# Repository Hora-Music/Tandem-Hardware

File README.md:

Here are the eagle files of the Tandem Module 
The firmware and the manual are available at https://github.com/Hora-Music/Tandem

This hardware design is released under CC BY-NC-SA 4.0 License.

It contains both the main board, the schematics and the panel.
Even the panel is a PCB so everything can be made by a classic PCB manufacturer. 
It is up to you to decide the layer you want to use for the yellow silkscreen, 
some manufacturers don't accept two silkscreen colors. In that case you can set it to a copper/pad layer. 

The design contains pretty common components and is build around a simple (and unexpensive :) ) stmf103CBT6

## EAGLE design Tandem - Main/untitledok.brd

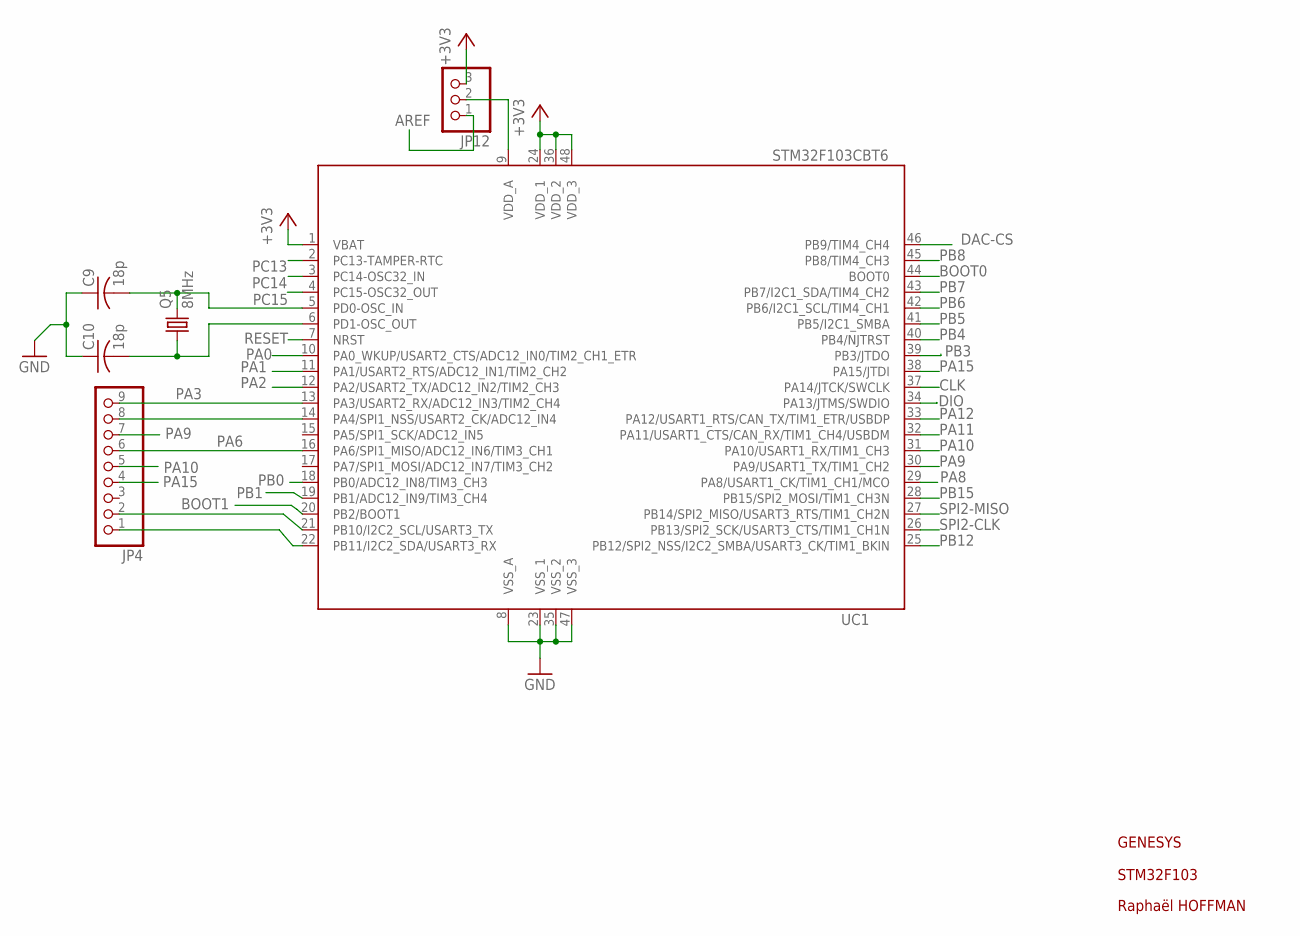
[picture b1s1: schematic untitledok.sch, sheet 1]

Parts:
C9, C10: 18p; C0603
JP4: PINHD-1X9; 1X09
JP12: PINHD-1X3; 1X03
Q5: 8MHz; HC49UP
UC1: STM32F103CBT6; LQFP48

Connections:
+3V3: JP12.3, UC1.1 (VBAT), UC1.24 (VDD_1), UC1.36 (VDD_2), UC1.48 (VDD_3); also elsewhere on the board
AREF: JP12.1; also elsewhere on the board
BOOT0: UC1.44 (BOOT0); also elsewhere on the board
BOOT1: UC1.20 (PB2/BOOT1); also elsewhere on the board
CLK: UC1.37 (PA14/JTCK/SWCLK); also elsewhere on the board
DAC-CS: UC1.46 (PB9/TIM4_CH4); also elsewhere on the board
DIO: UC1.34 (PA13/JTMS/SWDIO); also elsewhere on the board
GND: C9.1, C10.1, UC1.8 (VSS_A), UC1.23 (VSS_1), UC1.35 (VSS_2), UC1.47 (VSS_3); also elsewhere on the board
unnamed: JP12.2, UC1.9 (VDD_A)
unnamed: C9.2, Q5.2, UC1.5 (PD0-OSC_IN)
unnamed: C10.2, Q5.1, UC1.6 (PD1-OSC_OUT)
unnamed: JP4.1, UC1.22 (PB11/I2C2_SDA/USART3_RX)
unnamed: JP4.8, UC1.14 (PA4/SPI1_NSS/USART2_CK/ADC12_IN4)
unnamed: JP4.2, UC1.21 (PB10/I2C2_SCL/USART3_TX)
PA0: UC1.10 (PA0_WKUP/USART2_CTS/ADC12_IN0/TIM2_CH1_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); also elsewhere on the board
PA1: UC1.11 (PA1/USART2_RTS/ADC12_IN1/TIM2_CH2); also elsewhere on the board
PA2: UC1.12 (PA2/USART2_TX/ADC12_IN2/TIM2_CH3); also elsewhere on the board
PA3: JP4.9, UC1.13 (PA3/USART2_RX/ADC12_IN3/TIM2_CH4); also elsewhere on the board
PA6: JP4.6, UC1.16 (PA6/SPI1_MISO/ADC12_IN6/TIM3_CH1); also elsewhere on the board
PA8: UC1.29 (PA8/USART1_CK/TIM1_CH1/MCO); also elsewhere on the board
PA9: JP4.7, UC1.30 (PA9/USART1_TX/TIM1_CH2); also elsewhere on the board
PA10: JP4.5, UC1.31 (PA10/USART1_RX/TIM1_CH3); also elsewhere on the board
PA11: UC1.32 (PA11/USART1_CTS/CAN_RX/TIM1_CH4/USBDM); also elsewhere on the board
PA12: UC1.33 (PA12/USART1_RTS/CAN_TX/TIM1_ETR/USBDP); also elsewhere on the board
PA15: JP4.4, UC1.38 (PA15/JTDI)
PB0: UC1.18 (PB0/ADC12_IN8/TIM3_CH3); also elsewhere on the board
PB1: UC1.19 (PB1/ADC12_IN9/TIM3_CH4); also elsewhere on the board
PB3: UC1.39 (PB3/JTDO)
PB4: UC1.40 (PB4/NJTRST); also elsewhere on the board
PB5: UC1.41 (PB5/I2C1_SMBA); also elsewhere on the board
PB6: UC1.42 (PB6/I2C1_SCL/TIM4_CH1); also elsewhere on the board
PB7: UC1.43 (PB7/I2C1_SDA/TIM4_CH2); also elsewhere on the board
PB8: UC1.45 (PB8/TIM4_CH3); also elsewhere on the board
PB12: UC1.25 (PB12/SPI2_NSS/I2C2_SMBA/USART3_CK/TIM1_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); also elsewhere on the board
PB15: UC1.28 (PB15/SPI2_MOSI/TIM1_CH3N); also elsewhere on the board
PC13: UC1.2 (PC13-TAMPER-RTC); also elsewhere on the board
PC14: UC1.3 (PC14-OSC32_IN); also elsewhere on the board
PC15: UC1.4 (PC15-OSC32_OUT); also elsewhere on the board
RESET: UC1.7 (NRST); also elsewhere on the board
SPI2-CLK: UC1.26 (PB13/SPI2_SCK/USART3_CTS/TIM1_CH1N); also elsewhere on the board
SPI2-MISO: UC1.27 (PB14/SPI2_MISO/USART3_RTS/TIM1_CH2N); also elsewhere on the board

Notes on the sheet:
STM32F103
GENESYS
Raphaël HOFFMAN

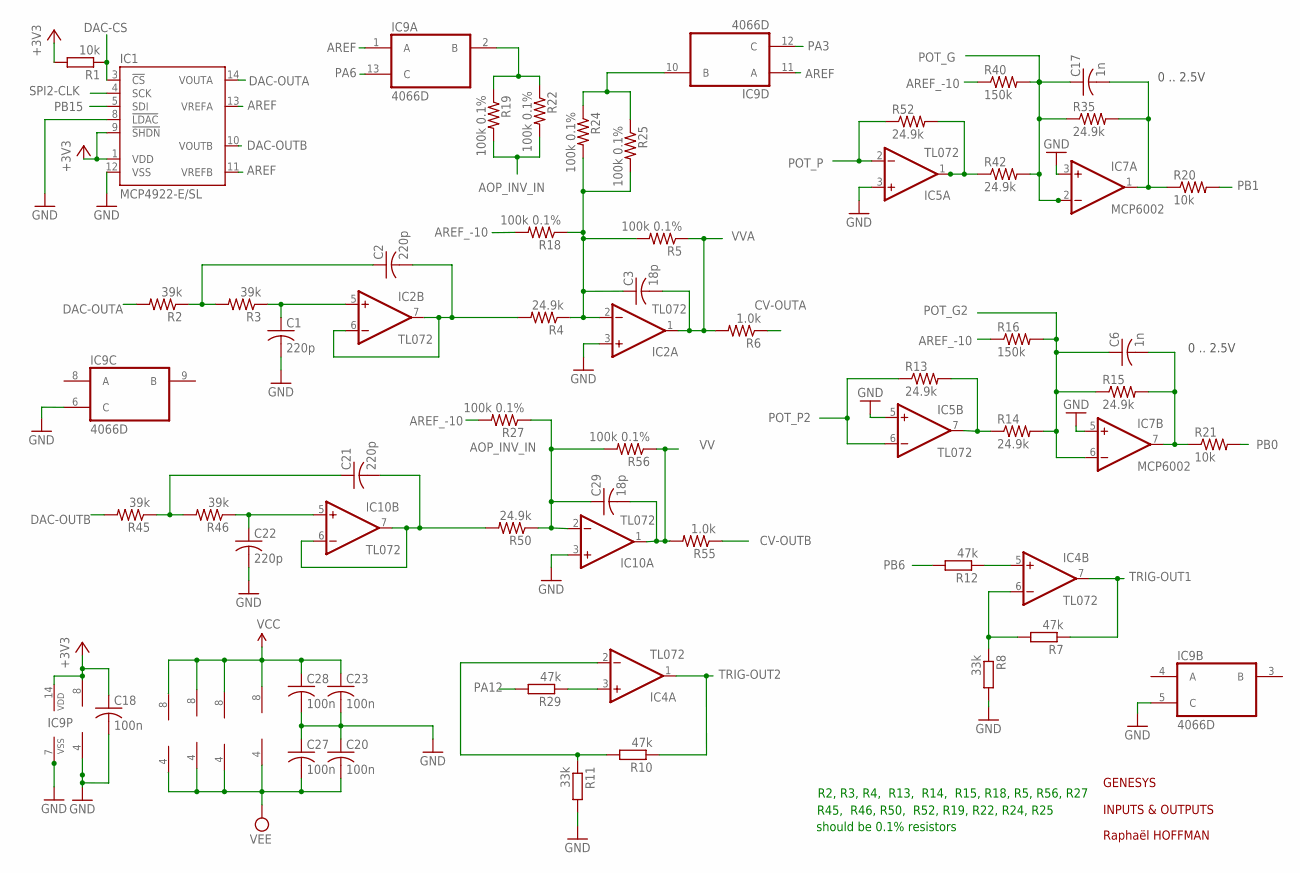
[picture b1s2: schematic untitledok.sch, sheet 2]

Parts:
C1, C2, C21, C22: 220p; C0603
C3, C29: 18p; C0603
C6, C17: 1n; C0603
C18, C20, C23, C27, C28: 100n; C0603
IC1: MCP4922-E/SL; SO14
IC2, IC4, IC5, IC10: TL072; SO08
IC7: MCP6002; SO08
IC9: 4066D; SO14
R1, R20, R21: 10k; R0603
R2, R3, R45, R46: 39k; R0603
R4, R13, R14, R15, R35, R42, R50, R52: 24.9k; R0603
R5, R18, R19, R22, R24, R25, R27, R56: 100k 0.1%; R0805
R6, R55: 1.0k; R0603
R7, R10, R12, R29: 47k; R0603
R8, R11: 33k; R0603
R16, R40: 150k; R0603

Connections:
+3V3: C18.1, IC1.1 (VDD), IC1.9 (!SHDN), IC7.8 (V+), IC9.14 (VDD), R1.2; also elsewhere on the board
AOP_INV_IN: C29.1, IC10.2 (-IN), R19.2, R22.2, R27.1, R50.1, R56.2
AREF: IC1.11 (VREFB), IC1.13 (VREFA), IC9.1 (A), IC9.11 (A); also elsewhere on the board
AREF_-10: R16.1, R18.2, R27.2, R40.1; also elsewhere on the board
CV-OUTA: R6.1; also elsewhere on the board
CV-OUTB: R55.1; also elsewhere on the board
DAC-CS: IC1.3 (!CS), R1.1; also elsewhere on the board
DAC-OUTA: IC1.14 (VOUTA), R2.2
DAC-OUTB: IC1.10 (VOUTB), R45.2
GND: C1.2, C18.2, C20.1, C22.2, C23.2, C27.1, C28.2, IC1.8 (!LDAC), IC1.12 (VSS), IC2.3 (+IN), IC5.3 (+IN), IC5.5 (+IN), IC7.3 (+IN), IC7.4 (V-), IC7.5 (+IN), IC9.5 (C), IC9.6 (C), IC9.7 (VSS), IC10.3 (+IN), R8.2, R11.2; also elsewhere on the board
unnamed: C2.2, IC2.6 (-IN), IC2.7 (OUT), R4.2
unnamed: C1.1, IC2.5 (+IN), R3.1
unnamed: C2.1, R2.1, R3.2
unnamed: IC4.3 (+IN), R29.1
unnamed: C3.1, IC2.2 (-IN), R4.1, R5.2, R18.1, R24.2, R25.2
unnamed: IC4.6 (-IN), R7.2, R8.1
unnamed: IC4.5 (+IN), R12.1
unnamed: IC5.7 (OUT), R13.2, R14.1
unnamed: IC9.2 (B), R19.1, R22.1
unnamed: IC4.2 (-IN), R10.2, R11.1
unnamed: IC9.10 (B), R24.1, R25.1
unnamed: IC5.1 (OUT), R42.1, R52.2
unnamed: C21.2, IC10.6 (-IN), IC10.7 (OUT), R50.2
unnamed: C22.1, IC10.5 (+IN), R46.1
unnamed: C21.1, R45.1, R46.2
P: C17.2, IC7.1 (OUT), R20.1, R35.2
PA3: IC9.12 (C); also elsewhere on the board
PA6: IC9.13 (C); also elsewhere on the board
PA12: R29.2; also elsewhere on the board
PB0: R21.2; also elsewhere on the board
PB1: R20.2; also elsewhere on the board
PB6: R12.2; also elsewhere on the board
PB15: IC1.5 (SDI); also elsewhere on the board
POT_G: C17.1, IC7.2 (-IN), R35.1, R40.2, R42.2; also elsewhere on the board
POT_G2: C6.1, IC7.6 (-IN), R14.2, R15.1, R16.2; also elsewhere on the board
POT_P: IC5.2 (-IN), R52.1; also elsewhere on the board
POT_P2: IC5.6 (-IN), R13.1; also elsewhere on the board
PPP: C6.2, IC7.7 (OUT), R15.2, R21.1
SPI2-CLK: IC1.4 (SCK); also elsewhere on the board
TRIG-OUT1: IC4.7 (OUT), R7.1; also elsewhere on the board
TRIG-OUT2: IC4.1 (OUT), R10.1; also elsewhere on the board
VCC: C23.1, C28.1, IC2.8 (V+), IC4.8 (V+), IC5.8 (V+), IC10.8 (V+); also elsewhere on the board
VEE: C20.2, C27.2, IC2.4 (V-), IC4.4 (V-), IC5.4 (V-), IC10.4 (V-); also elsewhere on the board
VV: C29.2, IC10.1 (OUT), R55.2, R56.1; also elsewhere on the board
VVA: C3.2, IC2.1 (OUT), R5.1, R6.2; also elsewhere on the board

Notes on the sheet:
0 .. 2.5V
INPUTS & OUTPUTS
GENESYS
Raphaël HOFFMAN
R2, R3, R4, R13, R14, R15, R18, R5, R56, R27
R45, R46, R50, R52, R19, R22, R24, R25
should be 0.1% resistors

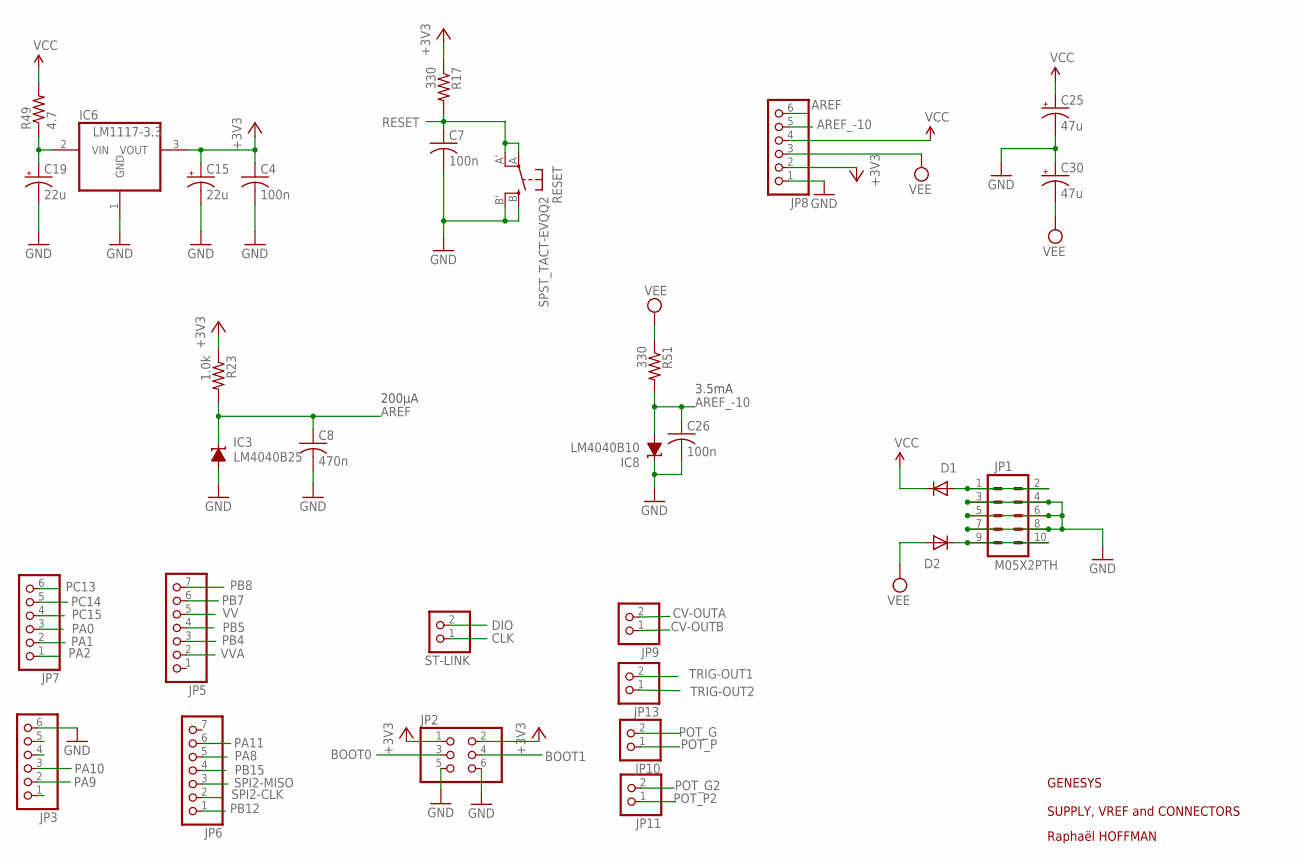
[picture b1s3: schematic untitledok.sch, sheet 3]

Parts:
C4, C7, C26: 100n; C0603
C8: 470n; C0603
C15, C19: 22u; PANASONIC_C
C25, C30: 47u; PANASONIC_D
D1, D2: 1N5819HW; SOD123
IC3: LM4040B25; DBZ_R-PDSO-G3
IC6: LM1117-3.3; TO252
IC8: LM4040B10; DBZ_R-PDSO-G3
JP1: M05X2PTH; AVR_ICSP
JP2: PINHD-2X3; 2X03
JP3, JP7, JP8: PINHD-1X6; 1X06
JP5, JP6: PINHD-1X7; 1X07
JP9, JP10, JP11, JP13: PINHD-1X2; 1X02
R17, R51: 330; R0603
R23: 1.0k; R0603
R49: 4.7; R1206
RESET: SPST_TACT-EVQQ2; EVQ-Q2
ST-LINK: PINHD-1X2; 1X02

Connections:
+3V3: C4.1, C15.+, IC6.3 (VOUT), JP2.1, JP2.2, JP8.2, R17.1, R23.1; also elsewhere on the board
AREF: C8.1, IC3.1 (C), JP8.6, R23.2; also elsewhere on the board
AREF_-10: C26.1, IC8.2 (A), JP8.5, R51.2; also elsewhere on the board
BOOT0: JP2.3; also elsewhere on the board
BOOT1: JP2.4; also elsewhere on the board
CLK: ST-LINK.1; also elsewhere on the board
CV-OUTA: JP9.2; also elsewhere on the board
CV-OUTB: JP9.1; also elsewhere on the board
DIO: ST-LINK.2; also elsewhere on the board
GND: C4.2, C7.2, C8.2, C15.-, C19.-, C25.-, C26.2, C30.+, IC3.2 (A), IC6.1 (GND), IC8.1 (C), JP1.3, JP1.4, JP1.5, JP1.6, JP1.7, JP1.8, JP2.5, JP2.6, JP3.6, JP8.1, RESET.B (S), RESET.B' (S1); also elsewhere on the board
unnamed: C19.+, IC6.2 (VIN), R49.1
unnamed: D1.A, JP1.1, JP1.2
unnamed: D2.C, JP1.9, JP1.10
PA0: JP7.3; also elsewhere on the board
PA1: JP7.2; also elsewhere on the board
PA2: JP7.1; also elsewhere on the board
PA8: JP6.5; also elsewhere on the board
PA9: JP3.2; also elsewhere on the board
PA10: JP3.3; also elsewhere on the board
PA11: JP6.6; also elsewhere on the board
PB4: JP5.3; also elsewhere on the board
PB5: JP5.4; also elsewhere on the board
PB7: JP5.6; also elsewhere on the board
PB8: JP5.7; also elsewhere on the board
PB12: JP6.1; also elsewhere on the board
PB15: JP6.4; also elsewhere on the board
PC13: JP7.6; also elsewhere on the board
PC14: JP7.5; also elsewhere on the board
PC15: JP7.4; also elsewhere on the board
POT_G: JP10.2; also elsewhere on the board
POT_G2: JP11.2; also elsewhere on the board
POT_P: JP10.1; also elsewhere on the board
POT_P2: JP11.1; also elsewhere on the board
RESET: C7.1, R17.2, RESET.A, RESET.A' (P1); also elsewhere on the board
SPI2-CLK: JP6.2; also elsewhere on the board
SPI2-MISO: JP6.3; also elsewhere on the board
TRIG-OUT1: JP13.2; also elsewhere on the board
TRIG-OUT2: JP13.1; also elsewhere on the board
VCC: C25.+, D1.C, JP8.4, R49.2; also elsewhere on the board
VEE: C30.-, D2.A, JP8.3, R51.1; also elsewhere on the board
VV: JP5.5; also elsewhere on the board
VVA: JP5.2; also elsewhere on the board

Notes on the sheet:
200µA
3.5mA
SUPPLY, VREF and CONNECTORS
GENESYS
Raphaël HOFFMAN

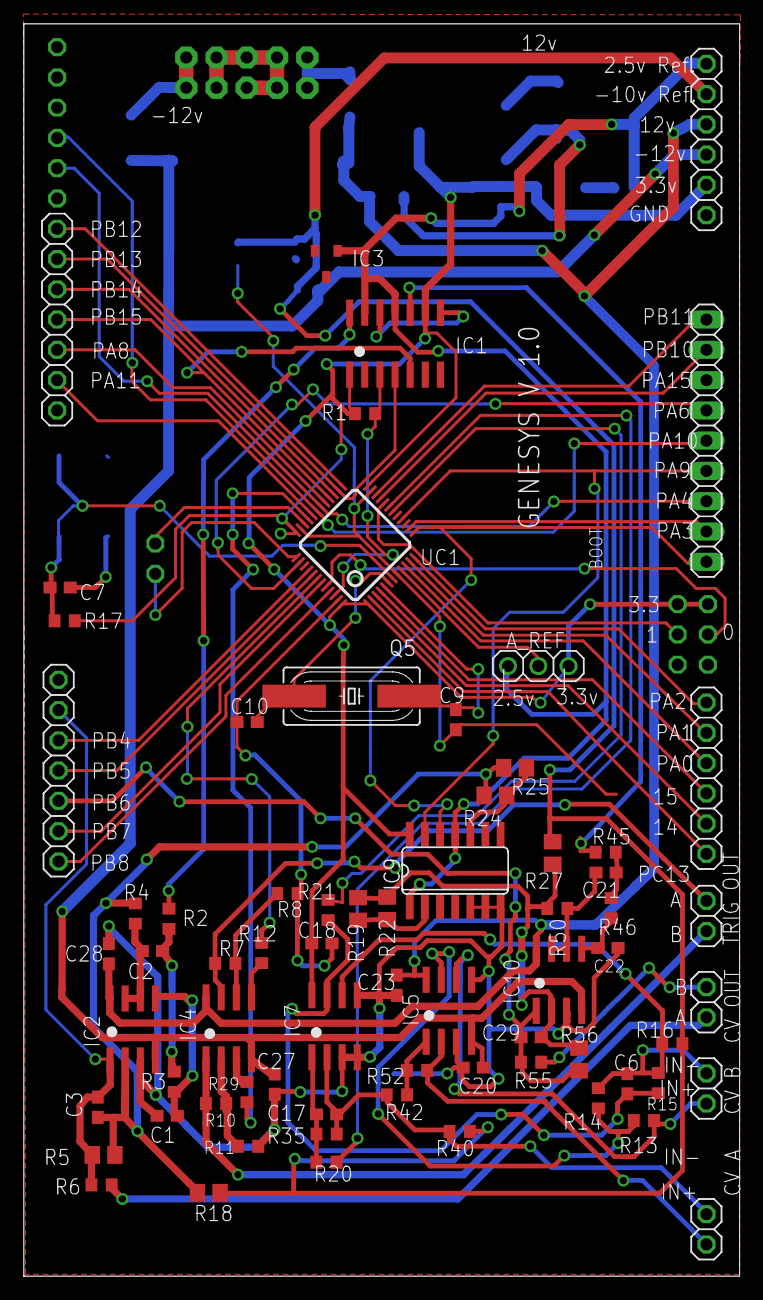
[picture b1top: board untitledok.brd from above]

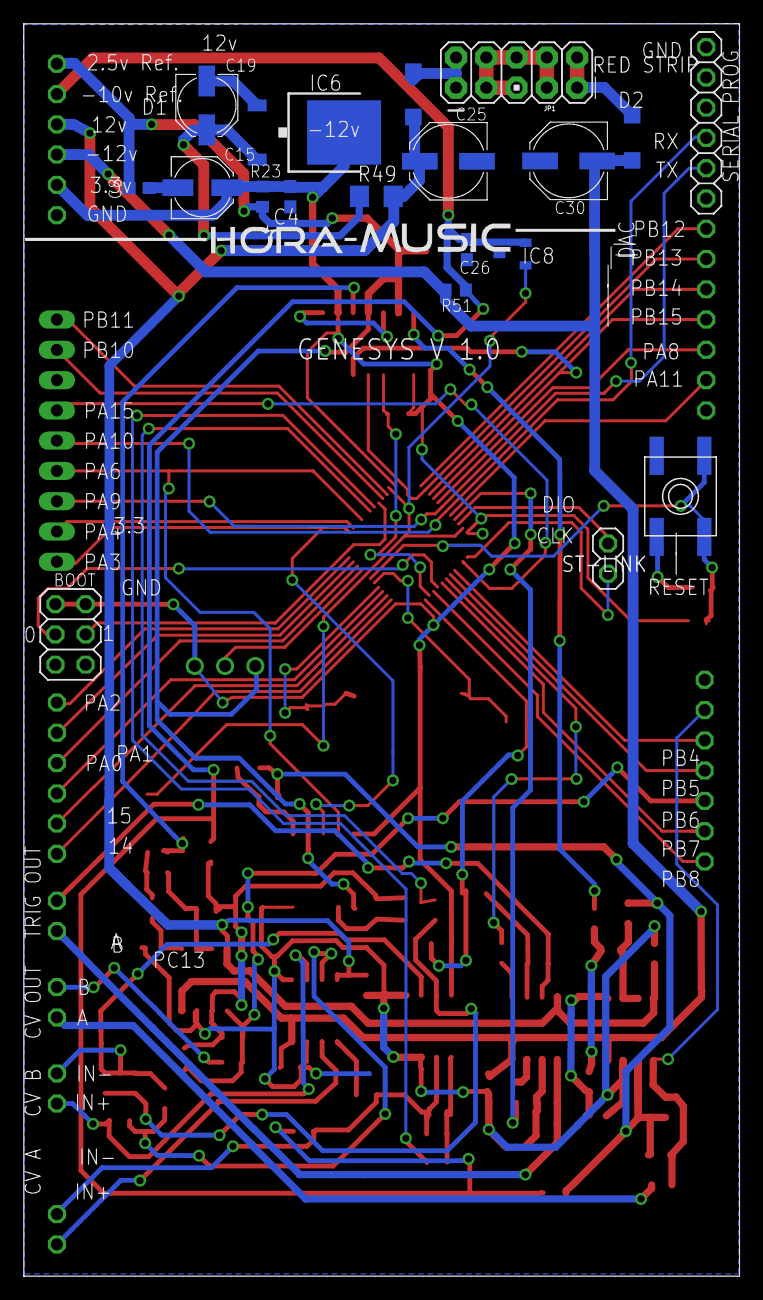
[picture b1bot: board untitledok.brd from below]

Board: 2 copper layers, 60.1 x 105.1 mm, 89 parts (19 on the bottom side), 76 nets.

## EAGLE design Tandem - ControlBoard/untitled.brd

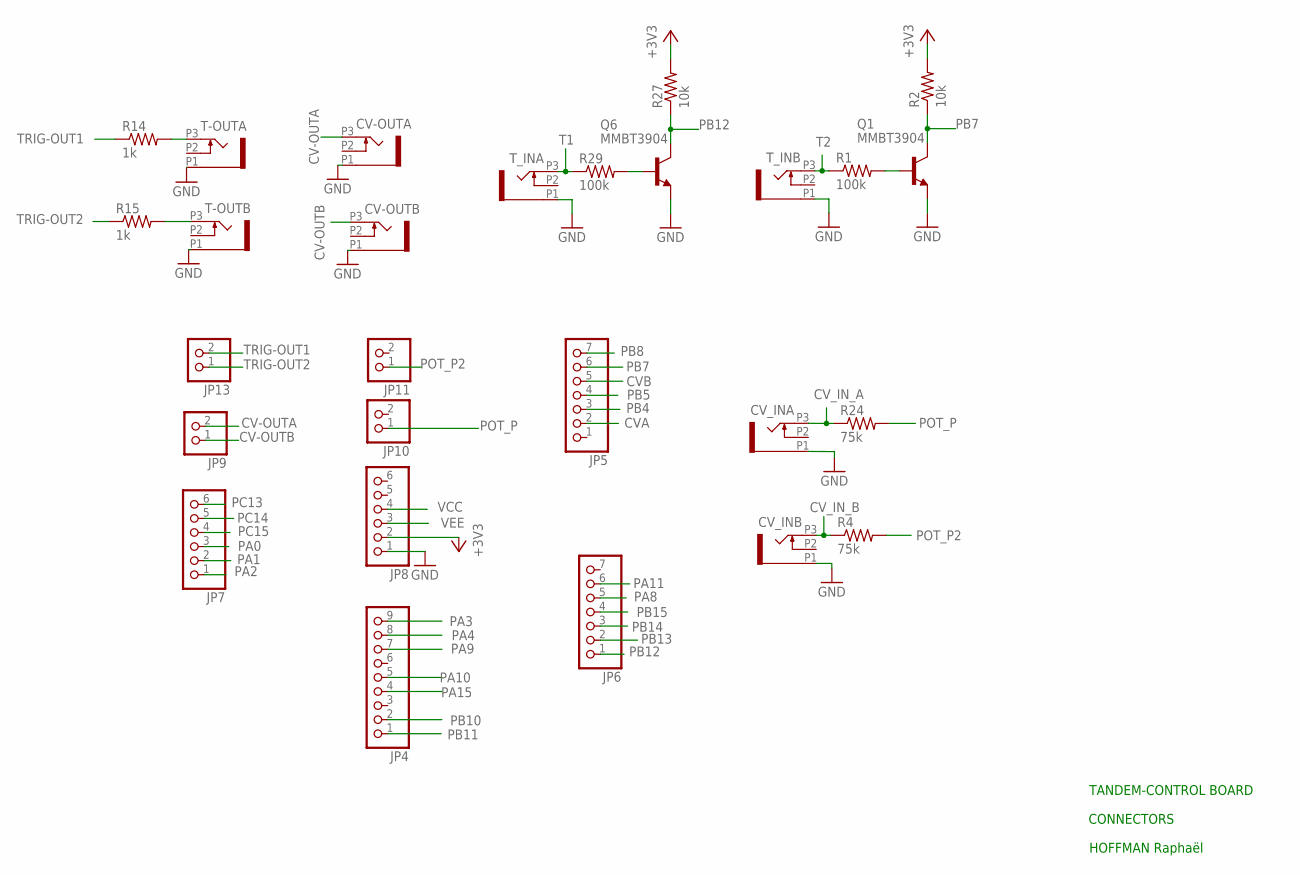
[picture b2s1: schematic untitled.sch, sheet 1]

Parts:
CV-OUTA: PJ301_THONKICONN6; WQP_PJ_301M6
CV-OUTB: PJ301_THONKICONN6; WQP_PJ_301M6
CV_INA: PJ301_THONKICONN6; WQP_PJ_301M6
CV_INB: PJ301_THONKICONN6; WQP_PJ_301M6
JP4: PINHD-1X9; 1X09-BIG
JP5, JP6: PINHD-1X7; 1X07
JP7, JP8: PINHD-1X6; 1X06
JP9, JP10, JP11, JP13: PINHD-1X2; 1X02
Q1, Q6: MMBT3904; SOT23-BEC
R1, R29: 100k; R0603
R2, R27: 10k; R0603
R4, R24: 75k; R0603
R14, R15: 1k; R0603
T-OUTA: PJ301_THONKICONN6; WQP_PJ_301M6
T-OUTB: PJ301_THONKICONN6; WQP_PJ_301M6
T_INA: PJ301_THONKICONN6; WQP_PJ_301M6
T_INB: PJ301_THONKICONN6; WQP_PJ_301M6

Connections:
+3V3: JP8.2, R2.2, R27.2; also elsewhere on the board
CV-OUTA: CV-OUTA.P3 (3), JP9.2
CV-OUTB: CV-OUTB.P3 (3), JP9.1
CVA: JP5.2; also elsewhere on the board
CVB: JP5.5; also elsewhere on the board
CV_IN_A: CV_INA.P3 (3), R24.1; also elsewhere on the board
CV_IN_B: CV_INB.P3 (3), R4.1; also elsewhere on the board
GND: CV-OUTA.P1 (1), CV-OUTB.P1 (1), CV_INA.P1 (1), CV_INB.P1 (1), JP8.1, Q1.E, Q6.E, T-OUTA.P1 (1), T-OUTB.P1 (1), T_INA.P1 (1), T_INB.P1 (1); also elsewhere on the board
unnamed: Q1.B, R1.2
unnamed: R14.2, T-OUTA.P3 (3)
unnamed: R15.2, T-OUTB.P3 (3)
unnamed: Q6.B, R29.2
PA0: JP7.3; also elsewhere on the board
PA1: JP7.2; also elsewhere on the board
PA2: JP7.1; also elsewhere on the board
PA3: JP4.9
PA4: JP4.8; also elsewhere on the board
PA8: JP6.5; also elsewhere on the board
PA9: JP4.7; also elsewhere on the board
PA10: JP4.5; also elsewhere on the board
PA11: JP6.6; also elsewhere on the board
PA15: JP4.4; also elsewhere on the board
PB4: JP5.3; also elsewhere on the board
PB5: JP5.4; also elsewhere on the board
PB7: JP5.6, Q1.C, R2.1
PB8: JP5.7; also elsewhere on the board
PB10: JP4.2; also elsewhere on the board
PB11: JP4.1; also elsewhere on the board
PB12: JP6.1, Q6.C, R27.1
PB13: JP6.2; also elsewhere on the board
PB14: JP6.3; also elsewhere on the board
PB15: JP6.4; also elsewhere on the board
PC13: JP7.6; also elsewhere on the board
PC14: JP7.5; also elsewhere on the board
PC15: JP7.4; also elsewhere on the board
POT_P: JP10.1, R24.2
POT_P2: JP11.1, R4.2
T1: R29.1, T_INA.P3 (3); also elsewhere on the board
T2: R1.1, T_INB.P3 (3); also elsewhere on the board
TRIG-OUT1: JP13.2, R14.1; also elsewhere on the board
TRIG-OUT2: JP13.1, R15.1; also elsewhere on the board
VCC: JP8.4; also elsewhere on the board
VEE: JP8.3; also elsewhere on the board

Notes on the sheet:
CONNECTORS
TANDEM-CONTROL BOARD
HOFFMAN Raphaël

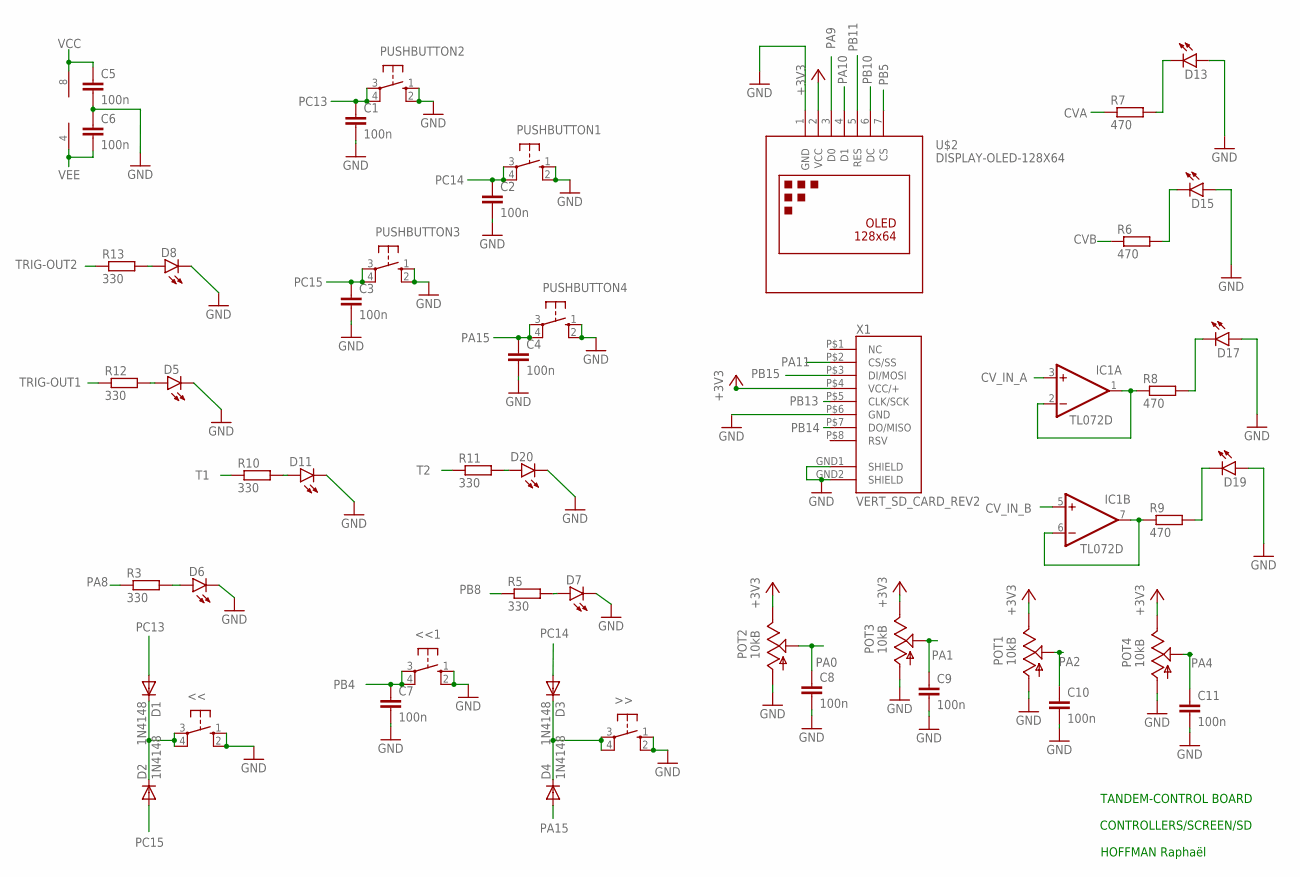
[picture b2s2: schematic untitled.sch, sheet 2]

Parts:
<<, <<1: 10-XX; B3F-10XX
>>: 10-XX; B3F-10XX
C1, C2, C3, C4, C5, C6, C7, C8, C9, C10, C11: 100n; C0603
D1, D2, D3, D4: 1N4148; DO35-7
D5, D6, D7, D8, D11, D13, D15, D17, D19, D20: LED3MM
IC1: TL072D; SO08
POT1, POT2, POT3, POT4: 10kB; EVUFXM
PUSHBUTTON1, PUSHBUTTON2, PUSHBUTTON3, PUSHBUTTON4: 10-XX; B3F-10XX
R3, R5, R10, R11, R12, R13: 330; R0603
R6, R7, R8, R9: 470; R0603
U$2: DISPLAY-OLED-128X64
X1: VERT_SD_CARD_REV2; VERT_MICROSD_REV2

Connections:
+3V3: POT1.3 (E), POT2.3 (E), POT3.3 (E), POT4.3 (E), U$2.2 (VCC), X1.P$4 (VCC/+); also elsewhere on the board
CVA: R7.1; also elsewhere on the board
CVB: R6.1; also elsewhere on the board
CV_IN_A: IC1.3 (+IN); also elsewhere on the board
CV_IN_B: IC1.5 (+IN); also elsewhere on the board
DD: >>.3, >>.4 (P1), D3.C, D4.C
DDD: <<.3, <<.4 (P1), D1.C, D2.C
GND: <<.1 (S), <<.2 (S1), <<1.1 (S), <<1.2 (S1), >>.1 (S), >>.2 (S1), C1.2, C2.2, C3.2, C4.2, C5.2, C6.1, C7.2, C8.2, C9.2, C10.2, C11.2, D5.K (C), D6.K (C), D7.K (C), D8.K (C), D11.K (C), D13.A, D15.A, D17.A, D19.A, D20.K (C), POT1.1 (A), POT2.1 (A), POT3.1 (A), POT4.1 (A), PUSHBUTTON1.1 (S), PUSHBUTTON1.2 (S1), PUSHBUTTON2.1 (S), PUSHBUTTON2.2 (S1), PUSHBUTTON3.1 (S), PUSHBUTTON3.2 (S1), PUSHBUTTON4.1 (S), PUSHBUTTON4.2 (S1), U$2.1 (GND), X1.GND1 (SHIELD), X1.GND2 (SHIELD), X1.P$6 (GND); also elsewhere on the board
unnamed: D20.A, R11.2
unnamed: D11.A, R10.2
unnamed: D5.A, R12.2
unnamed: D6.A, R3.2
unnamed: D15.K (C), R6.2
unnamed: D7.A, R5.2
unnamed: D8.A, R13.2
unnamed: D13.K (C), R7.2
unnamed: D17.K (C), R8.2
unnamed: IC1.1 (OUT), IC1.2 (-IN), R8.1
unnamed: D19.K (C), R9.2
unnamed: IC1.6 (-IN), IC1.7 (OUT), R9.1
PA0: C8.1, POT2.2 (S); also elsewhere on the board
PA1: C9.1, POT3.2 (S); also elsewhere on the board
PA2: C10.1, POT1.2 (S); also elsewhere on the board
PA4: C11.1, POT4.2 (S); also elsewhere on the board
PA8: R3.1; also elsewhere on the board
PA9: U$2.3 (D0); also elsewhere on the board
PA10: U$2.4 (D1); also elsewhere on the board
PA11: X1.P$2 (CS/SS); also elsewhere on the board
PA15: C4.1, D4.A, PUSHBUTTON4.3, PUSHBUTTON4.4 (P1); also elsewhere on the board
PB4: <<1.3, <<1.4 (P1), C7.1; also elsewhere on the board
PB5: U$2.7 (CS); also elsewhere on the board
PB8: R5.1; also elsewhere on the board
PB10: U$2.6 (DC); also elsewhere on the board
PB11: U$2.5 (RES); also elsewhere on the board
PB13: X1.P$5 (CLK/SCK); also elsewhere on the board
PB14: X1.P$7 (DO/MISO); also elsewhere on the board
PB15: X1.P$3 (DI/MOSI); also elsewhere on the board
PC13: C1.1, D1.A, PUSHBUTTON2.3, PUSHBUTTON2.4 (P1); also elsewhere on the board
PC14: C2.1, D3.A, PUSHBUTTON1.3, PUSHBUTTON1.4 (P1); also elsewhere on the board
PC15: C3.1, D2.A, PUSHBUTTON3.3, PUSHBUTTON3.4 (P1); also elsewhere on the board
T1: R10.1; also elsewhere on the board
T2: R11.1; also elsewhere on the board
TRIG-OUT1: R12.1; also elsewhere on the board
TRIG-OUT2: R13.1; also elsewhere on the board
VCC: C5.1, IC1.8 (V+); also elsewhere on the board
VEE: C6.2, IC1.4 (V-); also elsewhere on the board

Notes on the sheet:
CONTROLLERS/SCREEN/SD
TANDEM-CONTROL BOARD
HOFFMAN Raphaël

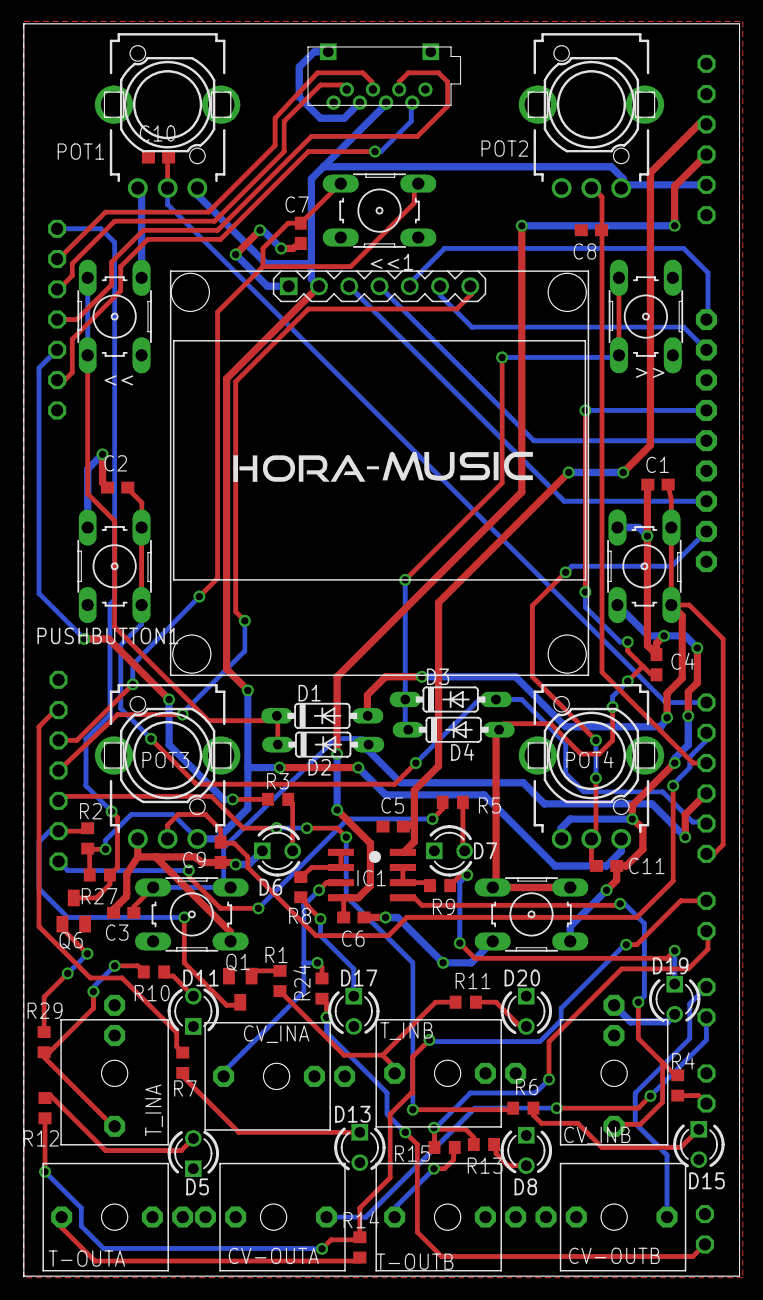
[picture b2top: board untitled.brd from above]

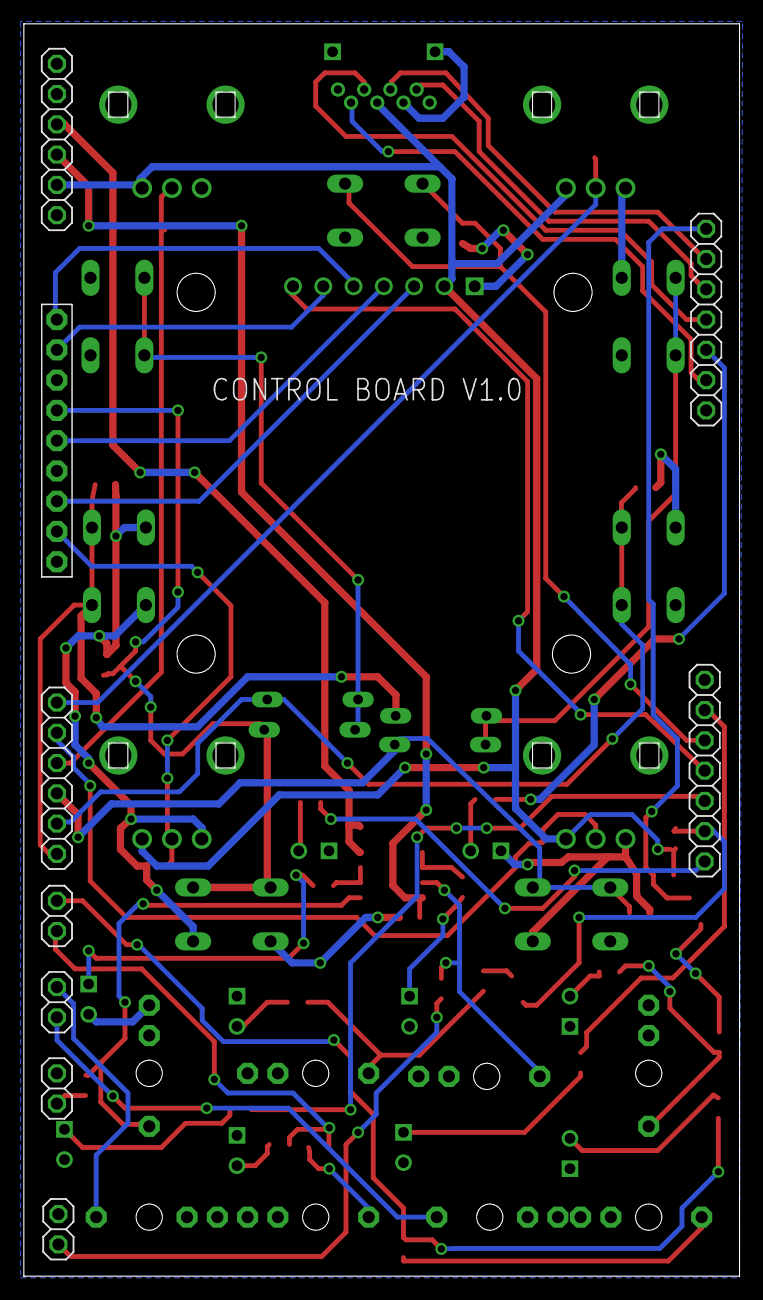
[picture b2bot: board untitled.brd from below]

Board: 2 copper layers, 60.1 x 105.1 mm, 76 parts (9 on the bottom side), 56 nets.

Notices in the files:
parts and their libraries:
diy-modules: Released under the Creative Commons Attribution 4.0 International License: http://creativecommons.org/licenses/by/4.0
